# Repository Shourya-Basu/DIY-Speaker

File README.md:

### Introduction 
Designed and validated an integrated Power Management Unit (PMU) from schematic to physical PCB, ensuring reliable energy storage and conversion for mobile device applications.

---

### Tech Stack

- Schematic – The blueprint stage where logical connections between components are defined using symbols, pins, and nets to create a functional electrical map.

- PCB Routing – The physical design process of laying down copper tracks (traces) on the board to connect components while adhering to design rules like clearance, trace width, and signal integrity.

- KiCad – An open-source EDA suite used for schematic capture and PCB layout, offering powerful tools for 3D visualization and Gerber file generation.
---

### Images

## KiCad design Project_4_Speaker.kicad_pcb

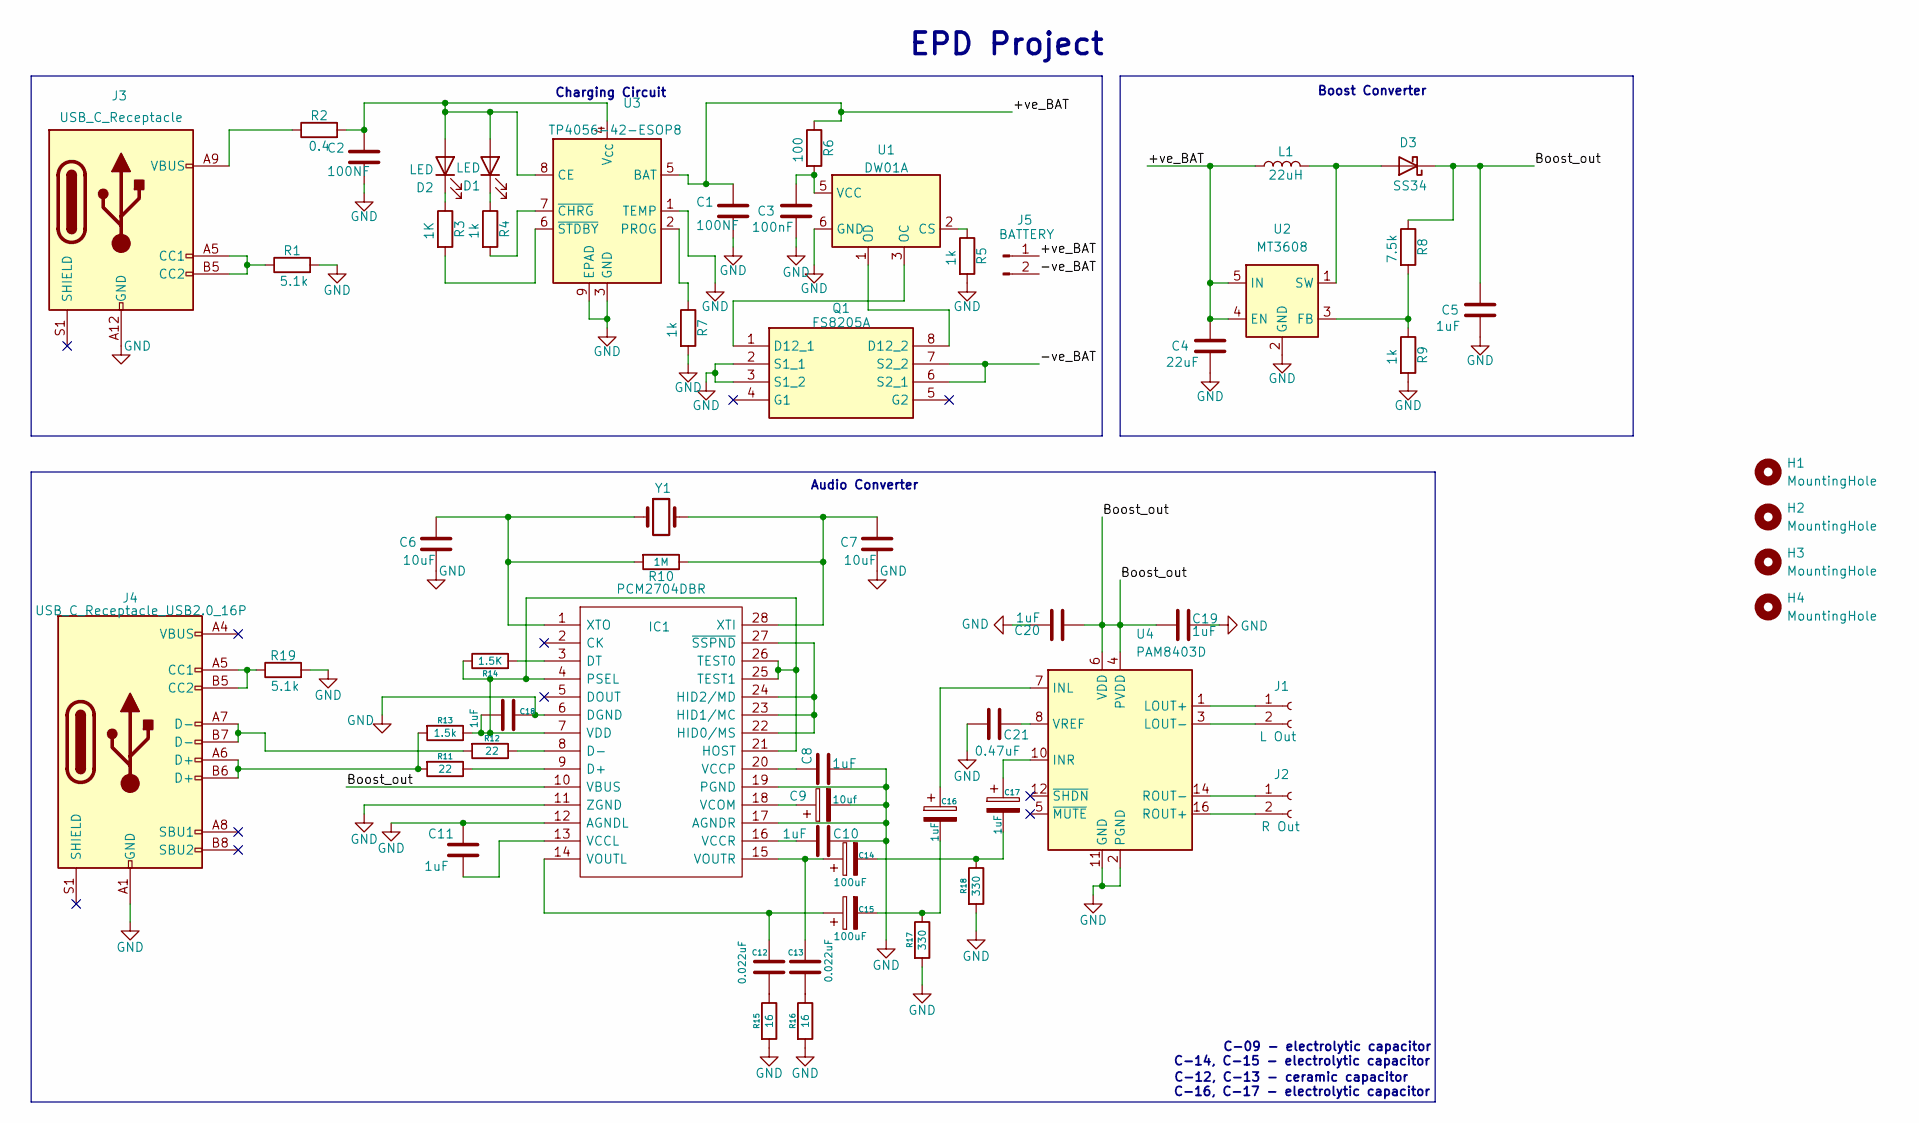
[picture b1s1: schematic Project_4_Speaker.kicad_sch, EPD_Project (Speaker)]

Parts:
C1, C2: 100NF; C_0805_2012Metric_Pad1.18x1.45mm_HandSolder
C3: 100nF; C_0805_2012Metric_Pad1.18x1.45mm_HandSolder
C4: 22uF; C_0805_2012Metric_Pad1.18x1.45mm_HandSolder
C5, C8, C10, C11, C18, C19, C20: 1uF; C_0805_2012Metric_Pad1.18x1.45mm_HandSolder
C6, C7: 10uF; C_0805_2012Metric_Pad1.18x1.45mm_HandSolder
C9: 10uf; CP_Radial_D4.0mm_P1.50mm
C12, C13: 0.022uF; C_0805_2012Metric_Pad1.18x1.45mm_HandSolder
C14, C15: 100uF; CP_Radial_D4.0mm_P1.50mm
C16, C17: 1uF; CP_Radial_D4.0mm_P1.50mm
C21: 0.47uF; C_0805_2012Metric_Pad1.18x1.45mm_HandSolder
D1, D2: LED; LED_0805_2012Metric_Pad1.15x1.40mm_HandSolder
D3: SS34; D_SMA
H1, H2, H3, H4: MountingHole; MountingHole_2.5mm
IC1: PCM2704DBR; SOP65P780X200-28N; Manufacturer_Part_Number PCM2704DBR; Mouser Part Number 595-PCM2704DBR
J1: L Out; Molex_KK-254_AE-6410-02A_1x02_P2.54mm_Vertical
J2: R Out; Molex_KK-254_AE-6410-02A_1x02_P2.54mm_Vertical
J3: USB_C_Receptacle; USB_C_Receptacle_GCT_USB4125-xx-x_6P_TopMnt_Horizontal
J4: USB_C_Receptacle_USB2.0_16P; USB_C_Receptacle_GCT_USB4085
J5: BATTERY; JST_EH_B2B-EH-A_1x02_P2.50mm_Vertical
L1: 22uH; L_10.4x10.4_H4.8
Q1: FS8205A; SOP65P640X120-8N; Manufacturer_Part_Number FS8205A
R1, R19: 5.1k; R_0805_2012Metric_Pad1.20x1.40mm_HandSolder
R2: 0.4; R_0805_2012Metric_Pad1.20x1.40mm_HandSolder
R3: 1K; R_0805_2012Metric_Pad1.20x1.40mm_HandSolder
R4, R5, R7, R9: 1k; R_0805_2012Metric_Pad1.20x1.40mm_HandSolder
R6: 100; R_0805_2012Metric_Pad1.20x1.40mm_HandSolder
R8: 7.5k; R_0805_2012Metric_Pad1.20x1.40mm_HandSolder
R10: 1M; R_0805_2012Metric_Pad1.20x1.40mm_HandSolder
R11, R12: 22; R_0805_2012Metric_Pad1.20x1.40mm_HandSolder
R13: 1.5k; R_0805_2012Metric_Pad1.20x1.40mm_HandSolder
R14: 1.5K; R_0805_2012Metric_Pad1.20x1.40mm_HandSolder
R15, R16: 16; R_0805_2012Metric_Pad1.20x1.40mm_HandSolder
R17, R18: 330; R_0805_2012Metric_Pad1.20x1.40mm_HandSolder
U1: DW01A; SOT-23-6
U2: MT3608; SOT-23-6
U3: TP4056-42-ESOP8; SOIC-8-1EP_3.9x4.9mm_P1.27mm_EP2.41x3.3mm
U4: PAM8403D; SO-16_3.9x9.9mm_P1.27mm
Y1: Crystal; Crystal_HC49-U_Vertical

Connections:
/+ve_BAT: C1.1, C4.1, J5.1, L1.1, R6.1, U2.4 (EN), U2.5 (IN), U3.5 (BAT)
/-ve_BAT: J5.2, Q1.6 (S2_1), Q1.7 (S2_2)
/Boost_out: C5.1, C19.1, C20.1, D3.1 (K), IC1.10 (VBUS), R8.1, U4.4 (PVDD), U4.6 (VDD), U4.13 (PVDD)
GND: C1.2, C2.2, C3.2, C4.2, C5.2, C6.2, C7.2, C8.2, C9.2, C10.1, C11.1, C18.1, C19.2, C20.2, C21.2, IC1.6 (DGND), IC1.11 (ZGND), IC1.12 (AGNDL), IC1.17 (AGNDR), IC1.19 (PGND), J3.A12 (GND), J3.B12 (GND), J4.A1 (GND), J4.A12 (GND), J4.B1 (GND), J4.B12 (GND), Q1.2 (S1_1), Q1.3 (S1_2), R1.2, R5.2, R7.2, R9.2, R15.2, R16.2, R17.2, R18.2, R19.2, U1.6 (GND), U2.2 (GND), U3.1 (TEMP), U3.3 (GND), U3.9 (EPAD), U4.2 (PGND), U4.11 (GND), U4.15 (PGND)
unnamed: C12.2, R15.1
unnamed: C13.2, R16.1
unnamed: C14.2, C17.2, R18.1
unnamed: C15.2, C16.2, R17.1
unnamed: C2.1, D1.2 (A), D2.2 (A), R2.2, U3.4 (V_{CC}), U3.8 (CE)
unnamed: D1.1 (K), R4.1
unnamed: D2.1 (K), R3.1
unnamed: D3.2 (A), L1.2, U2.1 (SW)
unnamed: IC1.9 (D+), R11.1
unnamed: IC1.8 (D-), R12.1
unnamed: IC1.3 (DT), R14.2
unnamed: IC1.22 (HID0/MS), IC1.23 (HID1/MC), IC1.24 (HID2/MD), IC1.27 (~SSPND)
unnamed: C18.2, IC1.4 (PSEL), IC1.7 (VDD), IC1.21 (HOST), IC1.25 (TEST1), IC1.26 (TEST0), R13.1, R14.1
unnamed: C11.2, IC1.13 (VCCL)
unnamed: C8.1, IC1.20 (VCCP)
unnamed: C10.2, IC1.16 (VCCR)
unnamed: C9.1, IC1.18 (VCOM)
unnamed: C12.1, C15.1, IC1.14 (VOUTL)
unnamed: C13.1, C14.1, IC1.15 (VOUTR)
unnamed: C7.1, IC1.28 (XTI), R10.1, Y1.2
unnamed: C6.1, IC1.1 (XTO), R10.2, Y1.1
unnamed: J1.1, U4.1 (LOUT+)
unnamed: J1.2, U4.3 (LOUT-)
unnamed: J2.1, U4.14 (ROUT-)
unnamed: J2.2, U4.16 (ROUT+)
unnamed: J3.A5 (CC1), J3.B5 (CC2), R1.1
unnamed: J3.A9 (VBUS), J3.B9 (VBUS), R2.1
unnamed: J4.A5 (CC1), J4.B5 (CC2), R19.1
unnamed: J4.A6 (D+), J4.B6 (D+), R11.2, R13.2
unnamed: J4.A7 (D-), J4.B7 (D-), R12.2
unnamed: Q1.1 (D12_1), U1.3 (OC)
unnamed: Q1.8 (D12_2), U1.1 (OD)
unnamed: R5.1, U1.2 (CS)
unnamed: C3.1, R6.2, U1.5 (VCC)
unnamed: R8.2, R9.1, U2.3 (FB)
unnamed: R7.1, U3.2 (PROG)
unnamed: R4.2, U3.7 (~CHRG)
unnamed: R3.2, U3.6 (~STDBY)
unnamed: C16.1, U4.7 (INL)
unnamed: C17.1, U4.10 (INR)
unnamed: C21.1, U4.8 (VREF)

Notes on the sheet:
C-12, C-13 - ceramic capacitor
Audio Converter
EPD Project
Charging Circuit
C-09 - electrolytic capacitor
C-14, C-15 - electrolytic capacitor
C-16, C-17 - electrolytic capacitor
Boost Converter

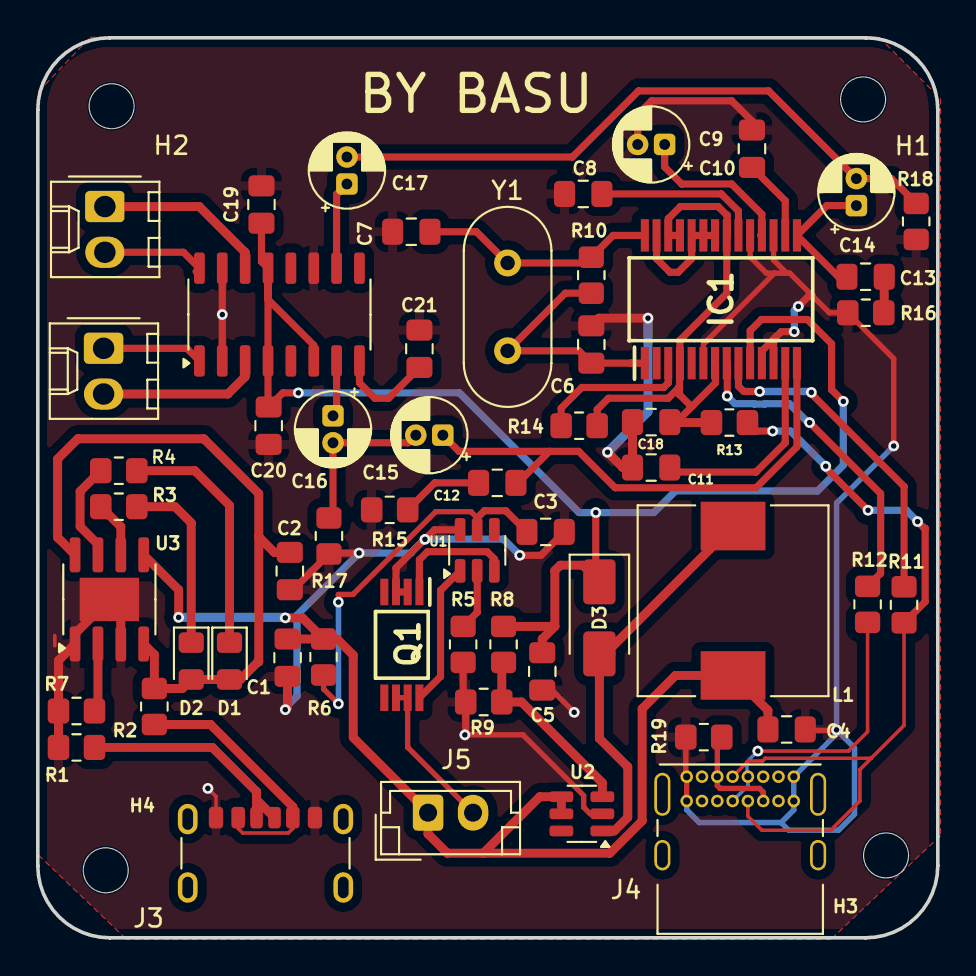
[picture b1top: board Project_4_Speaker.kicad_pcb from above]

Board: 2 copper layers, 50.0 x 50.0 mm, 60 parts (0 on the bottom side), 45 nets.

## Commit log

2025-09-17 README.md
2026-04-01 Add files via upload
    2025
2026-04-01 Rename Screenshot 2026-04-01 101331.png to 101.png
2026-04-01 Rename Screenshot 2026-04-01 101439.png to 102.png
2026-04-01 Rename Screenshot 2026-04-01 101514.png to 103.png
2026-04-01 Rename Screenshot 2026-04-01 101531.png to 104.png
2026-04-01 Rename Screenshot 2026-04-01 101624.png to 105.png
2026-04-01 Rename Screenshot 2026-04-01 101704.png to 106.png
